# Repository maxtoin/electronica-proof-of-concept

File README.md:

# Diseño electrónico para la *Prueba de concepto*
> Proyecto TeideSAT

## Introducción

En este repositorio pueden encontrarse todos los ficheros fuente para el desarrollo de la electrónica de los *dummies* de comunicaciones ópticas.

El diagrama de integración de elementos dentro del desarrollo electrónico es el mostrado a continuación:

## Herramientas y recursos utilizados

Las herramientas utilizadas para el desarrollo de la electrónica han sido las siguientes:

- [KiCAD](http://kicad-pcb.org/)
- [Libreoffice](https://es.libreoffice.org/)

## Módulos desarrollados

Los módulos electrónicos desarrollados en este repositorio son los siguientes:

- [ArduBoard](https://github.com/Teidesat/Electronica-proof-of-concept/tree/master/PCB/ArduBoard) - Módulo para el control de dispositivos a bajo nivel. Es el módulo encargado de enviar los pulsos codificados a los LED.

## Referencias

- [Github Brown Space Engineering](https://github.com/BrownSpaceEngineering)
- [Web Brown Space](https://brownspace.org/)

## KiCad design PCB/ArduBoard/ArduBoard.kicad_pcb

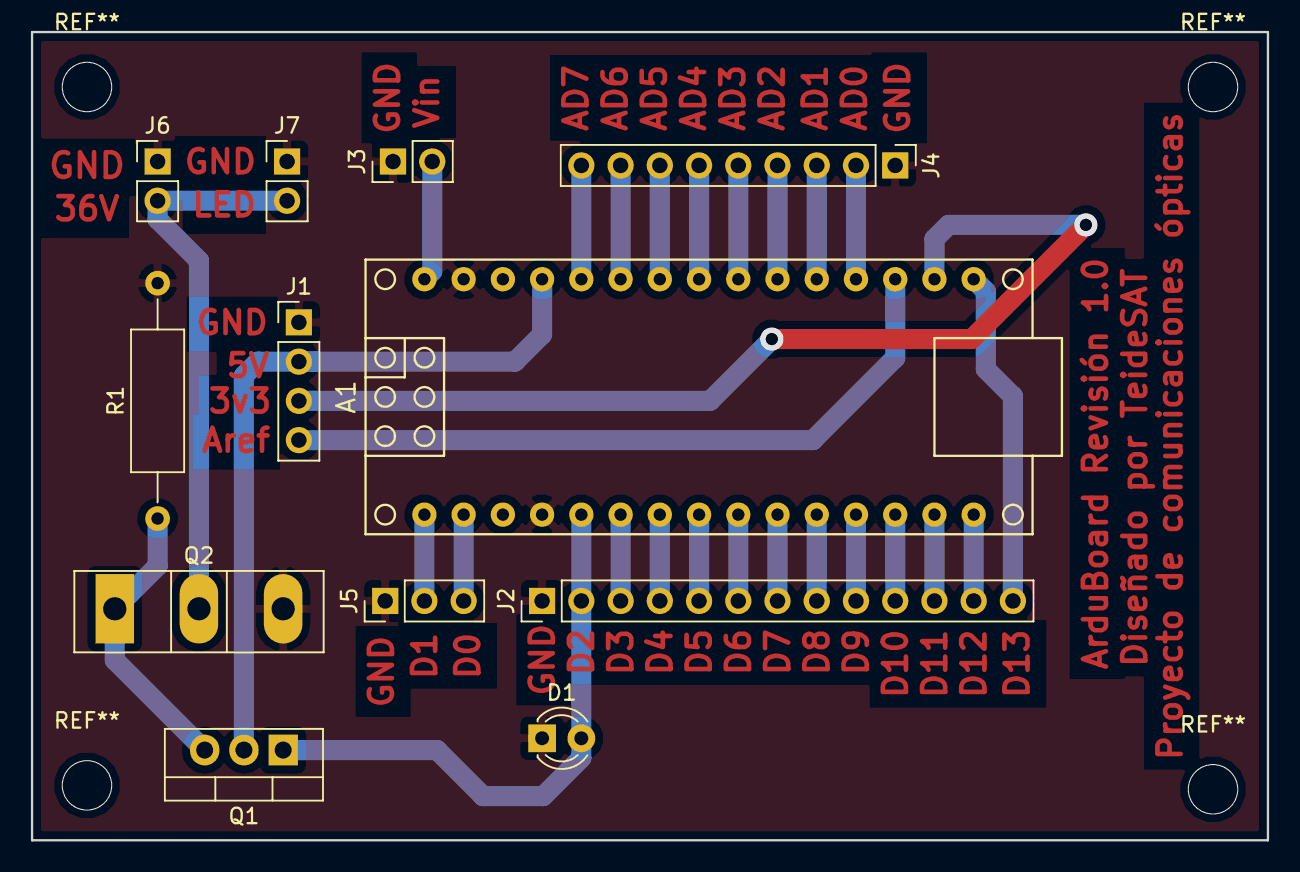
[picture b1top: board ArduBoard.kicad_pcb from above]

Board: 2 copper layers, 80.0 x 52.3 mm, 12 parts (0 on the bottom side), 29 nets.

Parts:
A1: Arduino_Nano; arduino_nano
D1: LED; LED_D3.0mm
J1: Conn_01x04_Male; PinHeader_1x04_P2.54mm_Vertical
J2: Conn_01x13_Male; PinHeader_1x13_P2.54mm_Vertical
J3, J6, J7: Conn_01x02_Male; PinHeader_1x02_P2.54mm_Vertical
J4: Conn_01x09_Male; PinHeader_1x09_P2.54mm_Vertical
J5: Conn_01x03_Male; PinHeader_1x03_P2.54mm_Vertical
Q1: Q_NMOS_GDS; TO-220-3_Vertical
Q2: Q_NIGBT_GCE; TO-247-3_Vertical
R1: 500k; R_Axial_DIN0309_L9.0mm_D3.2mm_P15.24mm_Horizontal

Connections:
5V: A1.27, J1.2, Q1.2
36V: J6.2, J7.2, Q2.2
AD0: A1.19, J4.2
AD1: A1.20, J4.3
AD2: A1.21, J4.4
AD3: A1.22, J4.5
AD4: A1.23, J4.6
AD5: A1.24, J4.7
AD6: A1.25, J4.8
AD7: A1.26, J4.9
CONTROL: Q1.3, Q2.1, R1.1
D0: A1.2, J5.3
D1: A1.1, J5.2
D2: A1.5, D1.2, J2.2, Q1.1
D3: A1.6, J2.3
D4: A1.7, J2.4
D5: A1.8, J2.5
D6: A1.9, J2.6
D7: A1.10, J2.7
D8: A1.11, J2.8
D9: A1.12, J2.9
D10: A1.13, J2.10
D11: A1.14, J2.11
D12: A1.15, J2.12
D13: A1.16, J2.13
GND: A1.4, A1.29, D1.1, J1.1, J2.1, J3.1, J4.1, J5.1, J6.1, J7.1, Q2.3, R1.2
unnamed: A1.17, J1.3
unnamed: A1.18, J1.4
unnamed: A1.30, J3.2

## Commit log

2018-08-02 Añadimos el README de referencia
2018-08-07 Corregimos el README
2018-08-07 Añadimos las referencias al README
2018-08-07 Añadimos los diagramas de referencia
2018-08-07 Añadimos un PNG del diagrama de integración de elementos
2018-08-07 Eliminamos los archivos temporales subidos por error
2018-08-07 Añadimos el diagrama de referencia al README
2018-08-07 Añadimos los datasheets de los led y las baterías
2018-08-07 Corregimos la alineación de la imagen en el readme
2018-08-07 Añadimos los datasheet del arduino nano y la raspberry pi
2018-08-16 Añadimos el proyecto de la placa de alimentación de los diodos
2018-08-16 Añadimos el índice de módulos desarrollados al README
2018-08-23 Añadimos las simulaciones
2018-08-23 Actualizados Datasheet
2018-08-23 Añadimos el modelo 3D del módulo
2018-08-30 Añadimos la versión corregida de la PCB (pistas en TOP y BOT)
2018-08-30 Añadimos los ficheros de fabricación del proyecto
2018-09-18 Añadimos la versión para la fabricación en la ProtoMat
2018-11-30 Añadimos el documento del cálculo de potencias
2018-11-30 Añadimos el pdf de prueba
2018-12-02 Añadimos las modificaciones sobre las potencias calculadas
2018-12-02 Añadimos el pdf de la especificación de potencias
2018-12-04 Create Documentacion
